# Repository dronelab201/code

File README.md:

# code
geotag on button press

# TODO
- Kicad 9.0.8
- sketch of circuit in pen and paper
- kicad format
- replace ESP32 with Raspberry Pi Pico
- Place PCB Order at Lion Circuites
- PCB Specs
- update code by removing TinyGPS libray with Sparkfun library

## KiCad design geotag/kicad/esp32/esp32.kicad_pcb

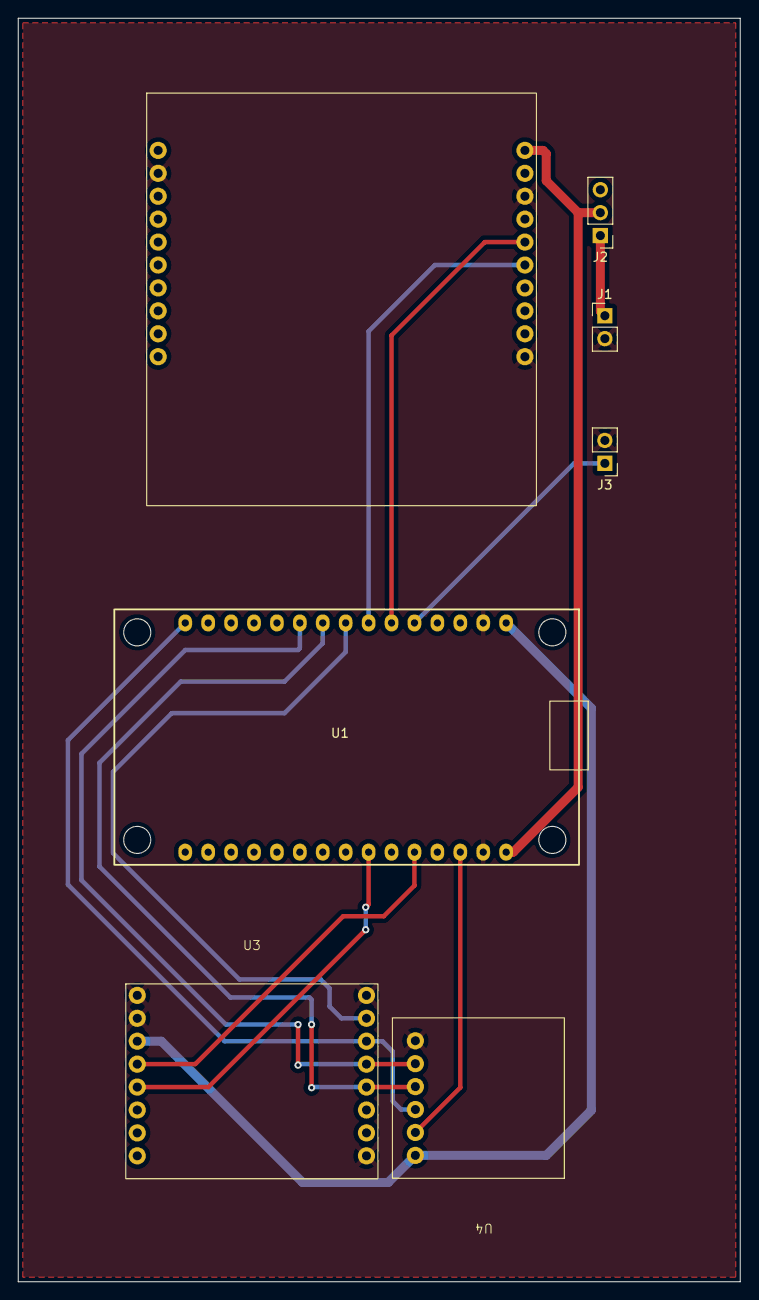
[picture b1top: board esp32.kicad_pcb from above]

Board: 2 copper layers, 80.0 x 140.0 mm, 7 parts (0 on the bottom side), 14 nets.

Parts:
J1: BTY; PinHeader_1x02_P2.54mm_Vertical
J2: SWITCH; PinHeader_1x03_P2.54mm_Vertical
J3: BTN; PinHeader_1x02_P2.54mm_Vertical
U1: ESP32_30pin
U2: 7SEMI UBLOX ZED F9P; 7SEMI_GPS
U3: LoRa Module; Lora Module
U4: SDCARD mODULE; SDCARD_MODULE

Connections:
/3V3: U1.16 (3.3v), U3.3 (3V3), U4.1 (3V3)
/5V: J2.2, U1.1 (VIN), U2.11 (5V)
/B+: J1.1, J2.1
/BTN: J3.1, U1.20 (GPIO4)
/CS: U1.3 (GPIO13), U4.2 (CS)
/GND: J1.2, J3.2, U1.2 (GND), U1.17 (GND), U2.2 (GND), U2.13 (GND), U2.20 (GND), U3.1 (GND), U3.2 (GND), U3.9 (GND), U3.16 (GND), U4.6 (GND)
/IO0: U1.7 (GPIO26), U3.5 (IO0)
/MISO: U1.25 (GPIO19), U3.12 (MISO), U4.5 (MISO)
/MOSI: U1.30 (GPIO23), U3.11 (MOSI), U4.3 (MOSI)
/NSS: U1.23 (GPIO5), U3.10 (NSS)
/RST: U1.5 (GPIO14), U3.4 (RST)
/RX2: U1.21 (GPIO16), U2.15 (TX2)
/SCK: U1.24 (GPIO18), U3.13 (SCK), U4.4 (CLK)
/TX2: U1.22 (GPIO17), U2.16 (RX2)

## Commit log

2026-03-18 Add files via upload
    arduino files
2026-03-19 restucture folder
2026-03-19 added kicad files
